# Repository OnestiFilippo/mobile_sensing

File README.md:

# Progetto Laboratorio Industria 4.0

## Mobile Sensing

Realizzazione di un sistema in grado di rilevare buche. 
Il sistema è composto da un dispositivo posizionabile su una bicicletta o un carretto, in grado di rilevare tramite un accelerometro la presenza di buche e la posizione esatta della rilevazione tramite un modulo GPS, e un componente server in grado di ricevere i dati dal dispositivo, di elaborarli e di permetterne la visualizzazione tramite un'interfaccia web.

## Installazione Componente Server

Per il componente server viene utilizzato docker per la creazione dei container necessari per la ricezione dei dati dal dispositivo e per la visualizzazione dei risultati nella pagina web dedicata.
Viene utilizzato un file docker-compose.yml per la creazione dei container. Vengono creati i container per la visualizzazione dei grafici tramite grafana e per la creazione del webserver Apache su cui è possibile accedere alle pagine web. 

```
version: "3.8"
services:
  grafana_mobile_sensing:
    image: grafana/grafana:latest
    container_name: grafana_mobile_sensing
    restart: unless-stopped
    ports:
     - '3003:3000'
  php_mobile_sensing:
    image: php:apache
    container_name: webserver_mobile_sensing
    restart: unless-stopped
    ports:
      - '8083:80'
    volumes:
      - /home/filippoonesti/mobile_sensing/html:/var/www/html/
  mqtt_mobile_sensing:
    image: filippoonesti/mobile_sensing_mqtt:latest
    container_name: mqtt_mobile_sensing
    restart: unless-stopped
    volumes:
      - /home/filippoonesti/mobile_sensing/html/records:/home/filippoonesti/mobile_sensing/html/records
```

Per eseguire il file docker-compose e per avviare i container si utilizza il seguente comando:

```
docker compose up -d
```

Una volta messi in esecuzione tutti i container necessari, è possibile accedere alla pagina web per la visualizzazione dei record all'indirizzo *http://localhost:8083*.

## Componente Client

La componente client del progetto consiste in un dispositivo hardware composto da un microcontrollore Raspberry Pi Pico W, un accelerometro, un modulo GPS, un display e due pulsanti.
Sul microcontrollore, tramite MicroPython, quando viene avviata la registrazione, vengono letti i dati dai sensori e, successivamente, vengono inviati alla componente Server tramite MQTT.
I file per l'esecuzione dello script MicroPython e le librerie necessarie sono all'interno della cartella `code_pico`.

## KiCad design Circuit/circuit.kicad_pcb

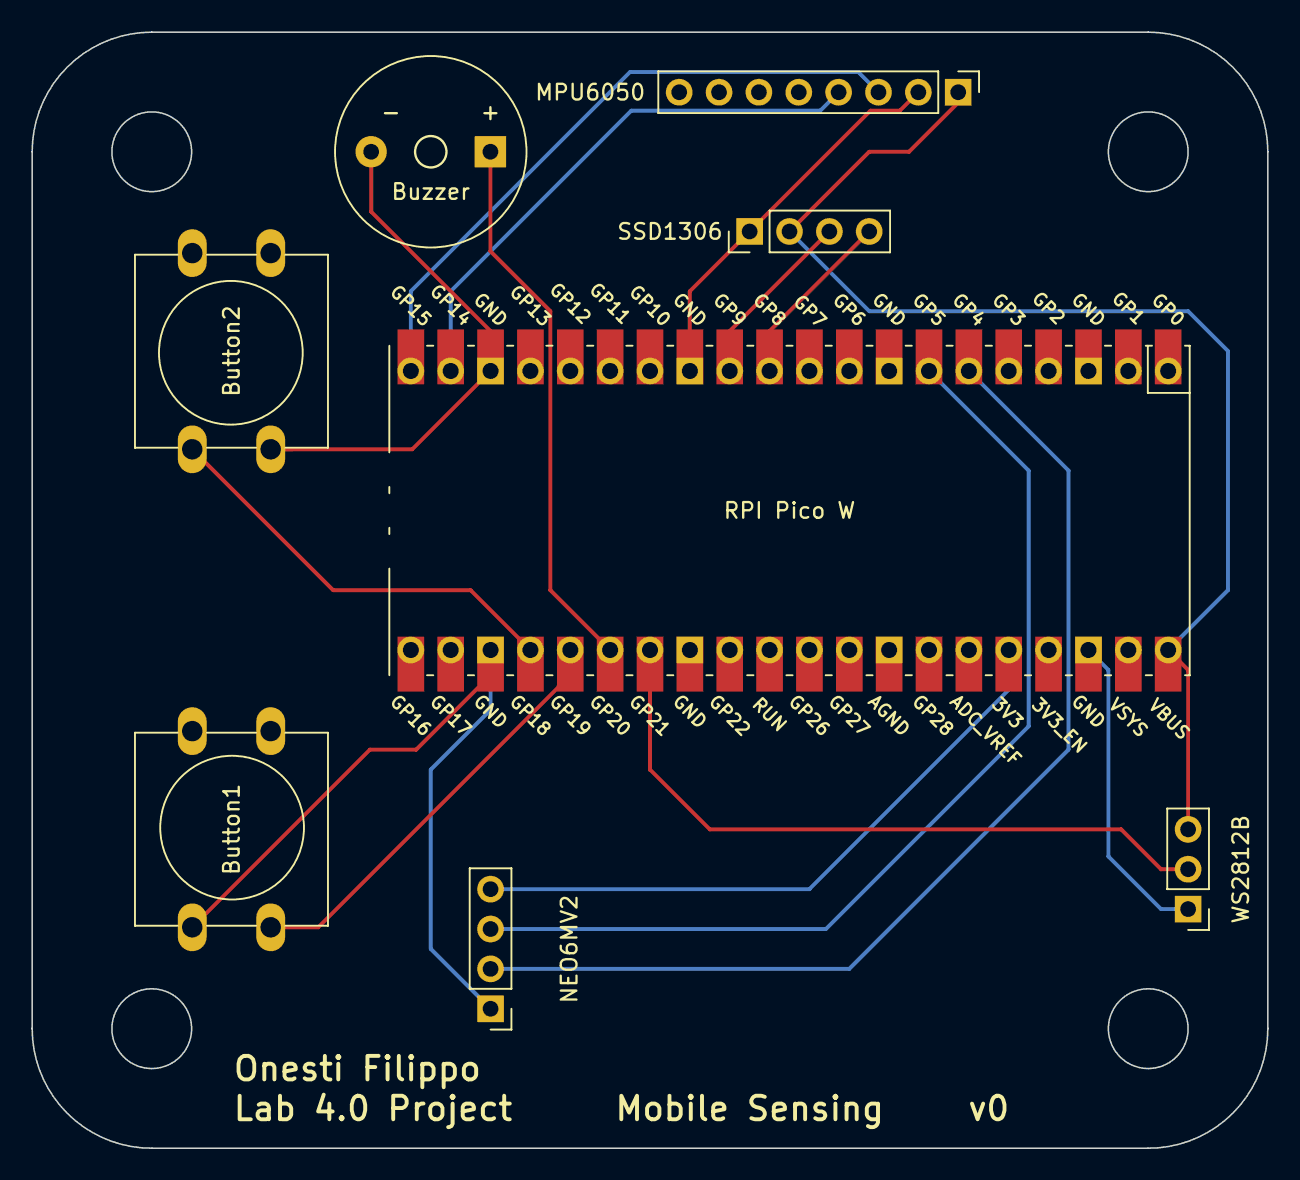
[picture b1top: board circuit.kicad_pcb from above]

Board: 2 copper layers, 78.7 x 71.1 mm, 8 parts (0 on the bottom side), 13 nets.

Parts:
J0: SSD1306; PinHeader_1x04_P2.54mm_Vertical
J1: NEO6MV2; PinHeader_1x04_P2.54mm_Vertical
J2: MPU6050; PinHeader_1x08_P2.54mm_Vertical
J3: WS2812B; PinHeader_1x03_P2.54mm_Vertical
J4: Button1; SW_PUSH-12mm
J5: Button2; SW_PUSH-12mm
J6: Buzzer; Buzzer_12x9.5RM7.6
U0: RPI Pico W; RPi_Pico_SMD_TH

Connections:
3.3V: J1.4, U0.36 (3V3)
5V: J0.2, J2.1, J3.3, U0.40 (VBUS)
BUT1: J5.2, U0.24 (GPIO18)
BUT2: J4.2, U0.25 (GPIO19)
BUZZ: J6.1, U0.26 (GPIO20)
GND: J0.1, J1.1, J2.2, J3.1, J4.1, J5.1, J6.2, U0.3 (GND), U0.8 (GND), U0.13 (GND), U0.18 (GND), U0.23 (GND), U0.28 (GND), U0.38 (GND)
LED: J3.2, U0.27 (GPIO21)
RX: J1.3, U0.7 (GPIO5)
SCL_ACC: J2.3, U0.20 (GPIO15)
SCL_DIS: J0.3, U0.12 (GPIO9)
SDA_ACC: J2.4, U0.19 (GPIO14)
SDA_DIS: J0.4, U0.11 (GPIO8)
TX: J1.2, U0.6 (GPIO4)

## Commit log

2024-05-03 README edited
2024-05-03 Added docker compose file and html folder
2024-05-03 Added index.html
2024-05-03 Updated index and created visualization
2024-05-04 Updated webpage and backend records managing
2024-05-08 Updated files to select a record to show
2024-05-14 Added MQTT files management
2024-05-14 Updated MQTT files management
2024-05-15 Updated files MQTT
2024-05-20 Added Dockerfile for MQTT Container
2024-05-24 Added ALL Visualization
2024-05-24 Added buttons style webpage
2024-05-31 Added Micropython Pico Files
2024-06-01 Added unit testing for mqttMS.py
2024-06-01 Removed old files
2024-06-11 Addedd PHP Unit Testing
2024-06-11 Fixed Python Tests
2024-06-11 Fixed PHP test
2024-06-19 Updated mqttMS.py
2024-06-20 Added Integration and Property Based Testing
2024-06-20 Added .gitignore
2024-07-01 Added test coverage
2024-08-19 Updated MQTT Python script
2024-08-22 Updated Pico files
